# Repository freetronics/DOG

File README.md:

DOG
===
http://www.freetronics.com/products/watchdog-timer-module

Design files for Freetronics watchdog timer module.

Connects to your Arduino or other microcontroller project and makes sure it keeps running by watching for a “heartbeat” signal. If the signal stops, the watchdog uses the microcontroller reset line to kick it back into life.

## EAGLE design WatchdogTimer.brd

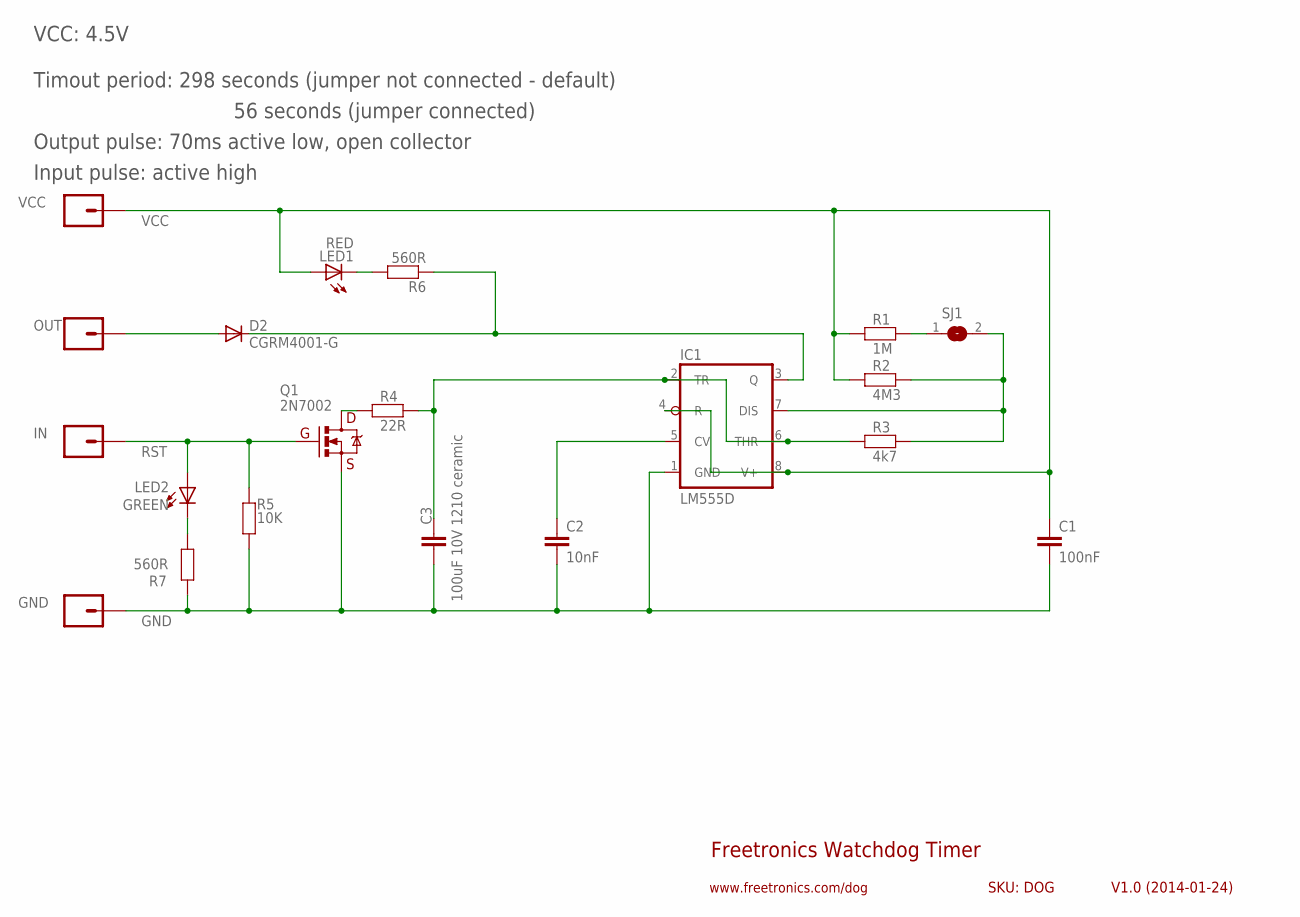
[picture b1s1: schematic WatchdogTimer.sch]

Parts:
C1: 100nF; 0603
C2: 10nF; 0603
C3: 100uF 10V 1210 ceramic; C1210
D2: CGRM4001-G; SOD-123_MINI-SMA
GND: M01PTH; 1X01
IC1: LM555D; SO08
IN: M01PTH; 1X01
LED1: RED; LED-0603
LED2: GREEN; LED-0603
OUT: M01PTH; 1X01
Q1: 2N7002; SOT23-3
R1: 1M; 0603
R2: 4M3; 0603
R3: 4k7; 0603
R4: 22R; 0603
R5: 10K; 0603
R6, R7: 560R; 0603
SJ1: SJ
VCC: M01PTH; 1X01

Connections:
C4: C3.1, IC1.2 (TR), IC1.6 (THR), R3.1, R4.2
GND: C1.2, C2.2, C3.2, GND.1, IC1.1 (GND), Q1.2 (S), R5.1, R7.2
unnamed: Q1.3 (D), R4.1
unnamed: LED2.C, R7.1
unnamed: R1.2, SJ1.1
unnamed: IC1.7 (DIS), R2.2, R3.2, SJ1.2
unnamed: LED1.C, R6.2
unnamed: C2.1, IC1.5 (CV)
unnamed: D2.A, OUT.1
RST: IN.1, LED2.A, Q1.1 (G), R5.2
TO: D2.C, IC1.3 (Q), R6.1
VCC: C1.1, IC1.4 (R), IC1.8 (V+), LED1.A, R1.1, R2.1, VCC.1

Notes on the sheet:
Freetronics Watchdog Timer
V1.0 (2014-01-24)
www.freetronics.com/dog
SKU: DOG
VCC: 4.5V
Timout period: 298 seconds (jumper not connected - default)
56 seconds (jumper connected)
Output pulse: 70ms active low, open collector
Input pulse: active high

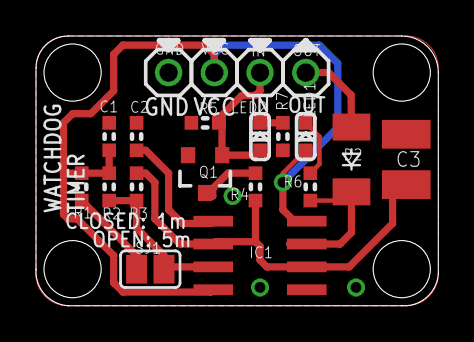
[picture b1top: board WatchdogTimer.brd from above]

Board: 2 copper layers, 22.4 x 15.0 mm, 20 parts (0 on the bottom side), 12 nets.

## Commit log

2013-12-15 Initial project
2014-01-24 Replaced main timing cap with 1206 tantalum for size reasons Updates to routing and labels
2014-10-07 Add schematic PDF
2014-10-07 Add README
2018-03-28 Improved parts designators

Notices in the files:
WatchdogTimer.brd:
(c) 2014 Freetronics
parts and their libraries:
freetronics-original: Licensing: CC v3.0 Share-Alike You are welcome to use this library for commercial purposes.
